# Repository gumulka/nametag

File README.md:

# Bluetooth ePaper Nametag

A simle project to show my name on an e-Paper

## How to build

If you are new to Zephyr, read the [Getting Started Guide](https://docs.zephyrproject.org/latest/develop/getting_started/index.html).
Afterwards you can clone and build this project with:

```bash
west init -m https://github.com/gumulka/nametag --mr main nametag
cd nametag
west update
cd epaper_nametag
```

### Bootloader

The bootloader will load and verify the image that is executed. To make it
easier to upgrade the device, two images are saved on the device and only one is
being executed, while the other is a standby for updating. The bootloader cannot
be upgraded via ble, but the image can be. Therefore making it possible to
upgrade devices in the field.

If you have a unprogrammed device, use this to build and flash the bootloader:

```bash
west build -p -b epaper_nametag -d build_mcuboot ../bootloader/mcuboot/boot/zephyr/ -- -DCONFIG_BOOT_SIGNATURE_TYPE_ECDSA_P256=y
west flash -d build_mcuboot
```

### Application

The application is different from the bootloader and is what is in need of
updates/upgrades.

```bash
west build -p -b epaper_nametag app -- -DOVERLAY_CONFIG="output.conf"
west flash
```

## Update via BLE

If you have an already running device and just want to upgrade to the latest
firmware.

Either with the nRF Connect App, which can be quite handy, or in the commandline
use these steps:

```bash
sudo mcumgr --conntype ble --connstring ctlr_name=hci0,peer_name='Nametag' image upload build/zephyr/zephyr.signed.bin
sudo mcumgr --conntype ble --connstring ctlr_name=hci0,peer_name='Nametag' image list
```

Use the second hash provided from the second command to alter the following:

```bash
sudo mcumgr --conntype ble --connstring ctlr_name=hci0,peer_name='Nametag' image test "HASH_FROM_OUTPUT"
sudo mcumgr --conntype ble --connstring ctlr_name=hci0,peer_name='Nametag' reset
# wait for the system to restart and if you are sure, that the update was successful then
sudo mcumgr  --conntype ble --connstring ctlr_name=hci0,peer_name='Nametag' image confirm "HASH_FROM_OUTPUT"
```

More information about the general procedure can be found [here](https://docs.zephyrproject.org/latest/samples/subsys/mgmt/mcumgr/smp_svr/README.html)
and [here](https://docs.zephyrproject.org/latest/services/device_mgmt/mcumgr.html)

> [!TIP]
> I have seen a few errors when trying to upload the image and found that it
> works best, if I cancel the upload command after a few seconds and restart it
> a few seconds later, basically splitting the upload into 4-5 chunks instead
> of uploading it as a whole.

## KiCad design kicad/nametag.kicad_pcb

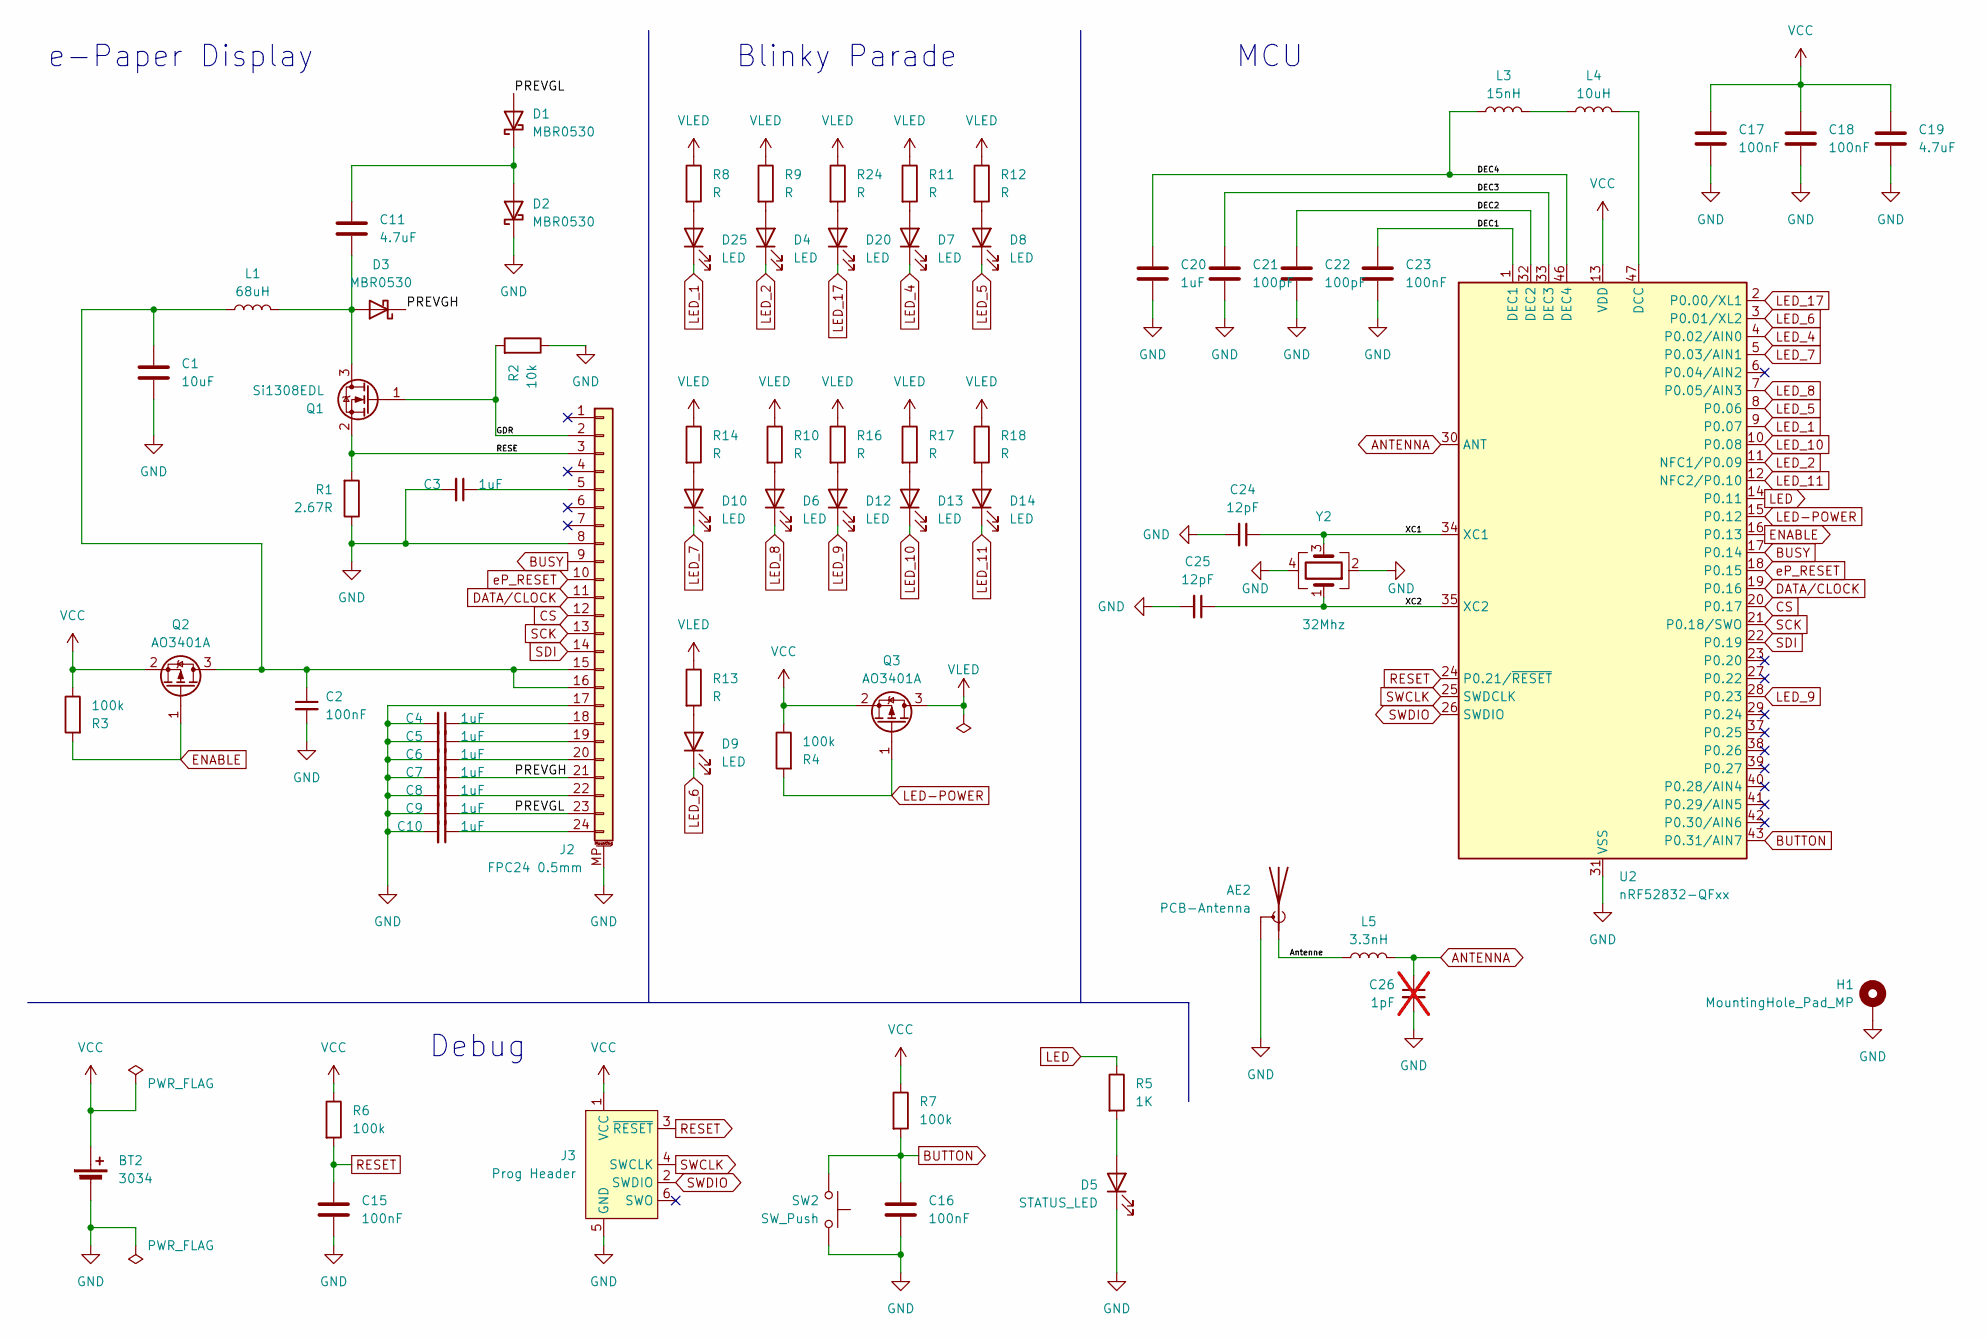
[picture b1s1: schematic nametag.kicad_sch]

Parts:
AE2: PCB-Antenna; Texas_SWRA117D_2.4GHz_Right
BT2: 3034; BatteryHolder_Keystone_3034_1x20mm; MPN 3034TR; LCSC# C5213768
C1: 10uF; C_0603_1608Metric
C2: 100nF; C_0402_1005Metric
C3, C4, C5, C6, C7, C8, C9, C10: 1uF; C_0603_1608Metric
C11: 4.7uF; C_0603_1608Metric
C15, C16, C17, C18, C23: 100nF; C_0402_1005Metric; MPN 100nF 0402; LCSC# C1525
C19: 4.7uF; C_0603_1608Metric; MPN 4,7uF 0603; LCSC# C19666
C20: 1uF; C_0603_1608Metric; MPN 1uF 0603; LCSC# C15849
C21, C22: 100pF; C_0402_1005Metric; MPN 100pF 0402; LCSC# C1546
C24, C25: 12pF; C_0402_1005Metric; MPN 12pF 0402; LCSC# C1547
C26: 1pF; C_0402_1005Metric; not fitted
D1, D2, D3: MBR0530; D_SOD-123
D4, D6, D7, D8, D9, D10, D12, D13, D14, D20, D25: LED; LTST-C230
D5: STATUS_LED; LED_0603_1608Metric; MPN KP-1608SGC; LCSC# C72043
H1: MountingHole_Pad_MP; Safety-pin
J2: FPC24 0.5mm; AMPHENOL_SFV24R-4STBE1HLF
J3: Prog Header; Tag-Connect_TC2030-IDC-NL_2x03_P1.27mm_Vertical
L1: 68uH; L_1210_3225Metric
L3: 15nH; L_0402_1005Metric; MPN LQW15AN15NH00D; LCSC# C27143
L4: 10uH; L_0603_1608Metric; MPN MLZ1608E100MT; LCSC# C1035
L5: 3.3nH; L_0402_1005Metric; MPN LQG15HS3N3C02D; LCSC# C14033
Q1: Si1308EDL; SOT-323_SC-70
Q2, Q3: AO3401A; SOT-23
R1: 2.67R; R_0603_1608Metric
R2: 10k; R_0603_1608Metric
R3, R4: 100k; R_0603_1608Metric
R5: 1K; R_0603_1608Metric; MPN 1K; LCSC# C11702
R6, R7: 100k; R_0603_1608Metric; MPN 100K; LCSC# C25741
R8, R9, R10, R11, R12, R13, R14, R16, R17, R18, R24: R; R_0603_1608Metric
SW2: SW_Push; SW_SPST_TL3342; MPN TS-1187A-B-A-B; LCSC# C318884
U2: nRF52832-QFxx; QFN-48-1EP_6x6mm_P0.4mm_EP4.6x4.6mm; MPN NRF52832-QFAA-R; LCSC# C77540
Y2: 32Mhz; Crystal_SMD_3225-4Pin_3.2x2.5mm; MPN X322532MOB4SI; LCSC# C9009

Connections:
/Antenne: AE2.1 (A), L5.2
/DEC1: C23.1, U2.1 (DEC1)
/DEC2: C22.1, U2.32 (DEC2)
/DEC3: C21.1, U2.33 (DEC3)
/DEC4: C20.1, L3.1, U2.46 (DEC4)
/GDR: J2.2, Q1.1 (G), R2.2
/PREVGH: C7.1, D3.1 (K), J2.21
/PREVGL: C9.1, D1.2 (A), J2.23
/RESE: J2.3, Q1.2 (S), R1.2
/XC1: C24.1, U2.34 (XC1), Y2.3
/XC2: C25.1, U2.35 (XC2), Y2.1
ANTENNA: C26.1, L5.1, U2.30 (ANT)
BUSY: J2.9, U2.17 (P0.14)
BUTTON: C16.1, R7.2, SW2.2, U2.43 (P0.31/AIN7)
CS: J2.12, U2.20 (P0.17)
DATA/CLOCK: J2.11, U2.19 (P0.16)
ENABLE: Q2.1 (G), R3.2, U2.16 (P0.13)
GND: AE2.2 (Shield), BT2.2 (-), C1.2, C2.2, C3.2, C4.2, C5.2, C6.2, C7.2, C8.2, C9.2, C10.2, C15.2, C16.2, C17.2, C18.2, C19.2, C20.2, C21.2, C22.2, C23.2, C24.2, C25.2, C26.2, D2.1 (K), D5.1 (K), H1.MP, J2.8, J2.17, J2.MP (MountPin), J3.5 (GND), R1.1, R2.1, SW2.1, U2.31 (VSS), U2.45 (VSS), U2.49 (VSS), Y2.2, Y2.4
LED: R5.1, U2.14 (P0.11)
LED-POWER: Q3.1 (G), R4.2, U2.15 (P0.12)
LED_1: D25.1 (K), U2.9 (P0.07)
LED_2: D4.1 (K), U2.11 (NFC1/P0.09)
LED_4: D7.1 (K), U2.4 (P0.02/AIN0)
LED_5: D8.1 (K), U2.8 (P0.06)
LED_6: D9.1 (K), U2.3 (P0.01/XL2)
LED_7: D10.1 (K), U2.5 (P0.03/AIN1)
LED_8: D6.1 (K), U2.7 (P0.05/AIN3)
LED_9: D12.1 (K), U2.28 (P0.23)
LED_10: D13.1 (K), U2.10 (P0.08)
LED_11: D14.1 (K), U2.12 (NFC2/P0.10)
LED_17: D20.1 (K), U2.2 (P0.00/XL1)
unnamed: C11.1, D1.1 (K), D2.2 (A)
unnamed: C11.2, D3.2 (A), L1.1, Q1.3 (D)
unnamed: D4.2 (A), R9.2
unnamed: D5.2 (A), R5.2
unnamed: D6.2 (A), R10.2
unnamed: D7.2 (A), R11.2
unnamed: D8.2 (A), R12.2
unnamed: D9.2 (A), R13.2
unnamed: D10.2 (A), R14.2
unnamed: D12.2 (A), R16.2
unnamed: D13.2 (A), R17.2
unnamed: D14.2 (A), R18.2
unnamed: D20.2 (A), R24.2
unnamed: D25.2 (A), R8.2
unnamed: C3.1, J2.5
unnamed: C1.1, C2.1, J2.15, J2.16, L1.2, Q2.3 (D)
unnamed: C4.1, J2.18
unnamed: C5.1, J2.19
unnamed: C6.1, J2.20
unnamed: C8.1, J2.22
unnamed: C10.1, J2.24
unnamed: L3.2, L4.1
unnamed: L4.2, U2.47 (DCC)
RESET: C15.1, J3.3 (~RESET), R6.2, U2.24 (P0.21/~RESET)
SCK: J2.13, U2.21 (P0.18/SWO)
SDI: J2.14, U2.22 (P0.19)
SWCLK: J3.4 (SWCLK), U2.25 (SWDCLK)
SWDIO: J3.2 (SWDIO), U2.26 (SWDIO)
VCC: BT2.1 (+), C17.1, C18.1, C19.1, J3.1 (VCC), Q2.2 (S), Q3.2 (S), R3.1, R4.1, R6.1, R7.1, U2.13 (VDD), U2.36 (VDD), U2.48 (VDD)
VLED: Q3.3 (D), R8.1, R9.1, R10.1, R11.1, R12.1, R13.1, R14.1, R16.1, R17.1, R18.1, R24.1
eP_RESET: J2.10, U2.18 (P0.15)

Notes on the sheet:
e-Paper Display
Blinky Parade
Debug
MCU

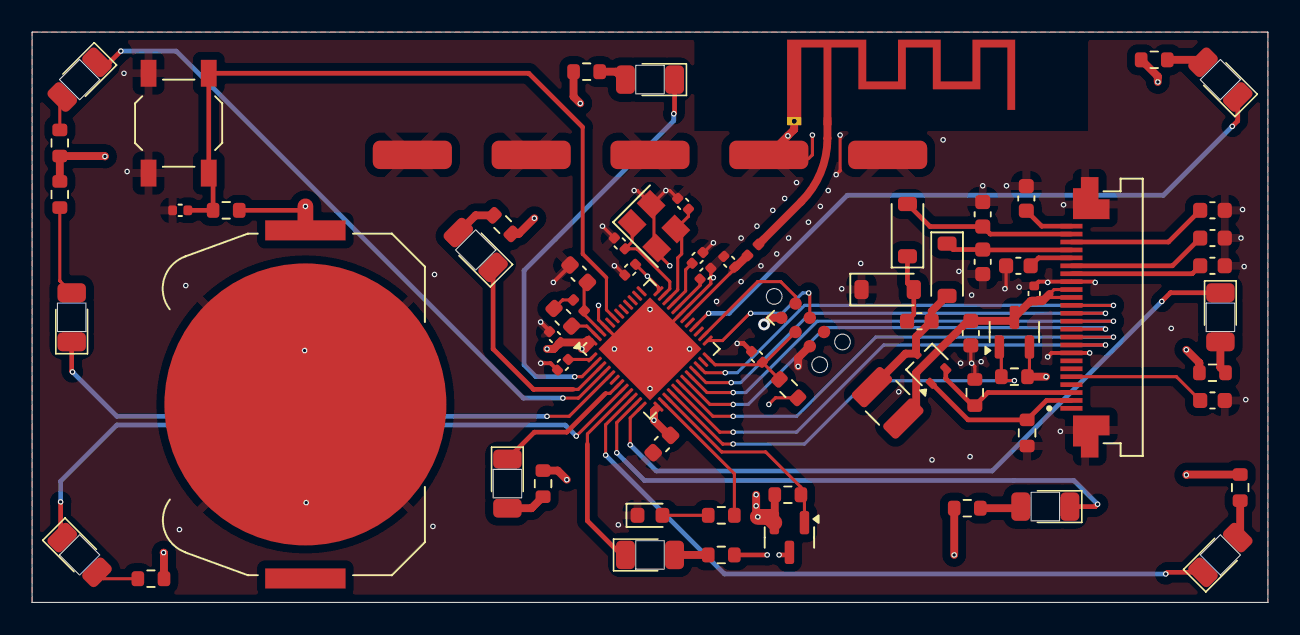
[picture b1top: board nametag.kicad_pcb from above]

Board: 4 copper layers, 78.0 x 36.0 mm, 71 parts (0 on the bottom side), 62 nets.

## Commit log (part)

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2024-08-28 Started to work on a nametag
    I want to have a bluetooth controlled e-paper nametag.
    And the ESP32 seems to be a bit to power hungry, but working with
    BLE and a nRF52832 might be just power efficient enough to work for a
    long time.
2024-09-03 First routing
    Did the routing for everything and made it somewhat useable.
    Have to sleep again for a night to see if I want to do it like this.
2024-09-03 Add Schematic for Waveshare ESP32 controller
    The board was hte inspiration and background for the schematic part of
    the e-paper controller.
2024-09-04 Last changes before ordering
2024-09-13 Add basic zephyr firmware
    Not more then the blinky sample, but a working blinky sample
    nonetheless :)
2024-09-20 Add support for Updates via BLE
2024-09-26 Add helper script to create image arrays
    Converting the image arrays to C arrays, that can be used inside the
    application
2024-09-26 Add first display variants
    Some basic information on what could be shown on the display.
2024-09-26 Add devicetree definition for e-Paper
    Tested the somewhat working code with the display example.
    But only add now the definitions of how to access the e-paper by
    looking at the code from waveshare and seeing on how to adapt it to the
    driver.
2024-09-26 Added 3D modeled case
    Modeled in FreeCad for a basic Case to support the device and display
2024-09-29 Iterate through screens with button
    Changing the screens on button press instead of a timer allows better
    control.
2024-09-29 Rotate display 180 degree
    because of course I got the orientation wrong...
